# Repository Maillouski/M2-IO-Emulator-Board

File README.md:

# M2 IO Emulator Board

**English** | [Français](README.fr.md)

A drop-in replacement for the **Sega 837-10539 I/O board** of the **Daytona USA twin** cabinet (Sega Model 2), built around an
**Arduino Mega 2560**. It lets an emulator drive the original cabinet: controls, lamps, meters, the original drive board (force
feedback) and the original arcade monitor.

> **Status: prototype.** The design passes DRC and ERC, but no board has been built or tested yet. Read
> [Open points](#open-points) before you order.

**Version: V3.2** (2026-10-16). V3 adds an [HDMI input](#hdmi-input-v3) with its own HDMI → VGA converter, a stereo audio
output and a [composite sync](#composite-sync) that no longer depends on the polarity of H and V. V2 (screen jumper JP8) is kept under the tag [`v2`](https://github.com/Maillouski/M2-IO-Emulator-Board/tree/v2), and V1,
the first board, ordered from JLCPCB on 2026-10-13, under the tag [`v1`](https://github.com/Maillouski/M2-IO-Emulator-Board/tree/v1).

## What it does

The idea is simple: pull the Sega I/O board out of the cabinet and put this one in its place. It has the same size, the same
mounting holes and the same connector names, so the original harness plugs straight in. Nothing gets cut or rewired.

Once it's in, the Arduino Mega becomes the bridge between the emulator and the cabinet. It reads the controls and drives
everything the original board used to drive:

- **Controls** — steering, accelerator, brake, shifter, coin, START, the VR view buttons, TEST and SERVICE.
- **Lamps, meters and relay** — switched by a ULN2803A, so the original bulbs and coin meters keep working.
- **Force feedback** — the original drive board stays in the cabinet and gets its commands from the Mega, so the wheel keeps
  its original force feedback.
- **Video** — an HDMI input (V3) or a VGA input goes to the original arcade monitor, with composite sync built on the board
  (negative, whatever the H/V polarity). A small switchable video amplifier lifts the signal to the level the tube expects.
- **Sound** — the audio carried by the HDMI input comes out on two RCA jacks (V3).

A few practical details make bring-up easier: TEST and SERVICE buttons right on the board, a power LED, test points for each
supply, and a jumper (JP1) to choose whether the drive board logic runs from the Mega's 5 V or from the cabinet's.

## Video jumpers

| VIDEO IN (J13) | JP2-JP4 (VIDEO AMP) | JP5-JP7 (VGA TERM 75 Ω) |
|---|---|---|
| PC / HDMI-VGA adapter | ON | ON |
| Arcade RGB | OFF | OFF |

The same table is printed on the board. With the HDMI input (V3), use the first row: U4 is the same kind of chip as the one inside an HDMI-to-VGA
adapter (not yet tried on a real board).

## Composite sync

U2 (74HCT86) builds the composite sync for the monitor from H and V, after the circuit of
[Tomi Engdahl](https://www.epanorama.net/circuits/vga2rgbs.html), pointed out by Zebidee on the ArcadeControls.com forum. Each sync is compared (XOR) with its own average, taken by an
RC filter (R66 + C47 for H, R67 + C48 for V: 2.2 kΩ, 22 µF), so its pulses always come out positive; the two are then combined
and inverted. The result is a **negative** composite sync whatever the polarity of H and V at the input, which is what the
original monitor expects. After a change of polarity (new video mode), the filters settle within a fraction of a second. It
goes to VIDEO OUT through R47 (470 Ω).

## HDMI input (V3)

New in V3. J15 takes the host's HDMI output directly; U4 (CS5213) turns it into analog R/G/B with H/V sync and stereo audio, so
no external HDMI → VGA adapter is needed. The VGA input J13 is still there, and a jumper chooses between the two.

| Jumper | Setting | Effect |
|---|---|---|
| JP9 (VIDEO INPUT SOURCE) | ON | video from the HDMI input (J15, through U4) |
| JP9 | OFF | video from the VGA input (J13), as on V2 |
| JP10 (HDMI CHIP 5V SELECT) | 1-2 | U4 runs from the Mega's 5 V |
| JP10 | 2-3 | U4 runs from the cabinet's 5 V, through a ferrite filter (FB1) |

- The switch is made by U7 (TS5V330, R/G/B) and U8 (74HCT157, H/V sync); everything after it (amplifier, composite sync, VIDEO
  OUT) is the same as on V2.
- **Audio:** J16, a stacked RCA jack: **top = left**, **bottom = right**, AC-coupled (10 µF in series). The footprint takes a
  Same Sky RCJ-2223 (DigiKey; red on top, so red = left) or a Lian Xin XDJK-0271-1650 (LCSC C7527522; white on top, red at the bottom).
- **Hot plug:** HPD is pulled up to the HDMI cable's 5 V, so the host sees a display as soon as the cable is in.
- **EDID:** U6, an AT24C02 EEPROM on the HDMI DDC lines (address 0x50, decoupled by C24), is fitted and comes **blank**; U4's own
  DDC pins are not connected. The host must write a 256-byte EDID into it (the monitor's video mode, and HDMI audio if wanted):
  while it is blank, the host reads an invalid EDID. Its write protect is tied low, so it is programmed in place, through the
  HDMI cable.
- **U5** is a second, not fitted, footprint for an NX3303X converter. Fit U4 or U5, never both.

## Screen jumper (JP8)

New in V2. JP8 ties the Mega's D36 pin to ground. The Mega reads it with its internal pull-up and sends it to the host with the
other inputs, so the host can choose its screen at start-up. Once the board is in the cabinet, switching screens only takes the
jumper, not a software change.

| JP8 | Screen |
|---|---|
| ON | CRT (4:3): the original arcade monitor, through the HDMI input (V3) or an HDMI-to-VGA adapter |
| OFF | LVDS panel (16:9) |

Printed on the board as SCREEN / ON = CRT (4:3) / OFF = LVDS 16:9. What the host does with this input is up to the host
software (see [Driving it from a computer](#driving-it-from-a-computer)).

## Driving it from a computer

The board comes with its Arduino Mega program ([`firmware/`](firmware/m2io-mega)) and a test console
([`tools/m2io_console.py`](tools/m2io_console.py)). To run Daytona USA on your own computer or emulator build and reach the
cabinet through this board, read **[Driving the board from your own host](docs/HOST-PROTOCOL.md)**: serial link, frames,
byte meanings, how to connect them to MAME's emulated I/O board, and the pitfalls to avoid.

## 3D views

Rendered with KiCad 10 from the files in this repository.

| | |
|---|---|
|  |  |
| Perspective view | Video section: VGA and HDMI inputs, source switch, OPA3355 amplifier, jumpers and settings tables |
|  |  |
| Top | Bottom |

## Repository

| Path | Contents |
|---|---|
| `kicad/` | KiCad 10 project: schematic, PCB, design rules, project footprint library (`interface-borne.pretty`), 3D models |
| `fabrication/` | Gerbers, Excellon drill files and drill maps (`gerbers/`), the same files zipped for the fab, pick-and-place file; JLCPCB BOM and CPL for SMD assembly ([`jlcpcb/`](fabrication/jlcpcb/README.md)) |
| `firmware/` | Arduino Mega program (`m2io-mega/`) and its PC test without a Mega (`test/`) |
| `tools/` | Test console: plays the host's part from any computer (Python 3 + pyserial) |
| `bom/` | Full BOM ([`BOM.md`](bom/BOM.md)) and DigiKey import file ([`BOM-digikey.csv`](bom/BOM-digikey.csv)) |
| `docs/` | [Host protocol](docs/HOST-PROTOCOL.md), schematic PDF, board renders |

Board: 2 layers, 180 × 190 mm. Gerbers come from the PCB's own plot settings (KiCad 10).

## Open points

- **V3 has not been built.** U4 (CS5213) has not been tried with the 24 kHz mode of the arcade monitor (its datasheet gives a
  25-200 MHz TMDS clock range); the HDMI pairs run on a 2-layer board without controlled impedance. V1 is the only board that
  has been ordered.
- **U4 is soldered by hand** and comes from a grey-market source (see the [BOM](bom/BOM.md#u4-cs5213)). Its exposed pad has vias:
  order "Epoxy Filled & Capped" vias or reduce the paste.
- **U5 (NX3303X):** its pinout comes from the maker's published pin diagram; it has not been checked on a real chip.
- **CN1 and CN2** are plain 3M four-wall headers, without ejector latches.

## 3D models

The Arduino Mega model in `kicad/3d/` is derived from Arduino's CAD files (CC BY-SA 4.0) and KiCad library models; see
[`kicad/3d/README.md`](kicad/3d/README.md). The JST NH connectors and the RCA jack (J16, drawn as the RCJ-2223) use simplified models made for this project.

## Credits

Sources used for this board: SEGA Daytona USA manuals; MAME (Dirk Best for the Model 1 I/O board; R. Belmont, O. Galibert,
ElSemi, A. Salese, M. Daniels for Model 2); M2Pac by BigPanik (Gamoover); DaytonaUSB by SailorSat; BackForceFeeder by njz3; MEGA
adapters by Tibal; the MiSTer project (video to arcade monitor); Tomi Engdahl (composite sync circuit); Zebidee on the ArcadeControls.com forum.

Not affiliated with or endorsed by SEGA.

## License

© 2026 Nicolas Mailloux. **CC BY-NC-SA 4.0** — see [`LICENSE`](LICENSE).
You may build, use, modify and share this board, as long as you credit the author, keep the credits, and share changes under the
same license. **No commercial use**: don't sell the board, the files or a derivative.
The firmware and the tools are under the same license.

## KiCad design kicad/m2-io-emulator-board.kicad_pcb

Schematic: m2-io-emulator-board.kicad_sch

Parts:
C1, C2, C3, C4, C5, C6, C7, C8, C9, C10, C11, C12, C13, C14, C15, C16, C18, C20, C21, C22, C24, C27, C28, C29, C31, C33, C35, C36, C38, C43, C44, C46: 100 nF; C_0805_2012Metric; MPN CC0805KRX7R9BB104
C17: 100 µF 16 V; CP_Radial_D6.3mm_P2.50mm; MPN EEU-FC1C101H
C19, C23, C25, C26, C30, C32, C34, C37, C41, C42, C45: 10 µF; C_0805_2012Metric; MPN CL21A106KAYNNNE
C39, C40: 10 nF; C_0805_2012Metric; MPN CC0805KRX7R9BB103
C47, C48: 22 µF; C_0805_2012Metric; MPN CL21A226MOCLRNC
D1: LED verte 3 mm; LED_D3.0mm; MPN_CMS_Flux LTST-C170KGKT
FB1: 600 Ω @ 100 MHz; L_0805_2012Metric; MPN GZ2012D601TF
J1: N2550-6002-RB; IDC-Header_2x25_P2.54mm_Vertical; MPN N2550-6002-RB
J2: N2526-6002-RB; IDC-Header_2x13_P2.54mm_Vertical; MPN N2526-6002-RB
J3: B10P-SHF-1AA; JST_NH_B10P-SHF-1AA_1x10_P2.50mm_Vertical; MPN B10P-SHF-1AA
J4, J5: B12P-SHF-1AA; JST_NH_B12P-SHF-1AA_1x12_P2.50mm_Vertical; MPN B12P-SHF-1AA
J6, J7, J8, J9, J10: 61300811121; PinHeader_1x08_P2.54mm_Vertical; MPN 61300811121
J11: 61301011121; PinHeader_1x10_P2.54mm_Vertical; MPN 61301011121
J12: Pin Header 02x18 2.54mm Vertical; PinHeader_2x18_P2.54mm_Vertical; MPN Pin Header 02x18 2.54mm Vertical
J13: VGA femelle; DSUB-15-HD_Socket_Horizontal_P2.29x2.54mm_EdgePinOffset8.35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; MPN L77HDE15SD1CH4F
J14: VIDEO; JST_NH_B5P-SHF-1AA_1x05_P2.50mm_Vertical; MPN B5P-SHF-1AA
J15: HDMI A; HDMI_A_Amphenol_10029449-x01xLF_Horizontal; MPN 10029449-111RLF
J16: XDJK-0271-1650; RCA_Dual_Stacked_RCJ-22xx_XDJK-0271-1650; MPN XDJK-0271-1650
JP1, JP2, JP3, JP4, JP10: 61300311121; PinHeader_1x03_P2.54mm_Vertical; MPN 61300311121
JP5, JP6, JP7, JP8, JP9: 61300211121; PinHeader_1x02_P2.54mm_Vertical; MPN 61300211121
R1, R2, R3, R4, R5, R6, R7, R8, R9, R10, R11, R12, R13: 4,7 kΩ; R_0805_2012Metric; MPN RC0805FR-074K7L
R14, R15, R16, R17, R18, R19, R20, R21, R22, R23, R24, R25, R26, R27, R28, R29, R30, R31, R32, R33, R34, R35, R36, R37, R46, R60: 1 kΩ; R_0805_2012Metric; MPN RC0805FR-071KL
R38, R39, R40, R41, R42, R43, R44, R45, R61, R62, R63, R64, R65: 10 kΩ; R_0805_2012Metric; MPN RC0805FR-0710KL
R47: 470 Ω; R_0805_2012Metric; MPN RMCF0805FT470R
R48, R49, R50: 75 Ω; R_0805_2012Metric; MPN RC0805FR-0775RL
R51, R52, R53: 604 Ω; R_0805_2012Metric; MPN RC0805FR-07604RL
R54, R55, R56: 200 Ω; R_0805_2012Metric; MPN RC0805FR-07200RL
R57, R58, R59: 33 Ω; R_0805_2012Metric; MPN RC0805FR-0733RL
R66, R67: 2,2 kΩ; R_0805_2012Metric; MPN RC0805FR-072K2L
SH1, SH2, SH3, SH4, SH5, SH6, SH7, SH8, SH9, SH10: 382811-8; MPN 382811-8
SW1: TEST; SW_PUSH_6mm; MPN 1825910-6
SW2: SERVICE; SW_PUSH_6mm; MPN 1825910-6
TP1, TP2, TP3, TP4: 5002; TestPoint_Keystone_5000-5004_Miniature; MPN 5002
U1: ULN2803A; DIP-18_W7.62mm; MPN ULN2803A
U2: 74HCT86; SOIC-14_3.9x8.7mm_P1.27mm; MPN 74HCT86D,653
U3: OPA3355EA; TSSOP-14_4.4x5mm_P0.65mm; MPN OPA3355EA/2K5
U4: CS5213; QFN-32-1EP_4x4mm_P0.4mm_EP2.65x2.65mm; MPN CS5213AN
U5: NX3303X; QFN-32-1EP_5x5mm_P0.5mm_EP3.1x3.1mm; MPN NX3303X; not fitted
U6: AT24C02; SOIC-8_3.9x4.9mm_P1.27mm; MPN AT24C02C-SSHM-T
U7: TS5V330; TSSOP-16_4.4x5mm_P0.65mm; MPN TS5V330CPWR
U8: 74HCT157; SOIC-16_3.9x9.9mm_P1.27mm; MPN SN74HCT157DR

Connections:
/+5V_BORNE: C17.1, C18.1, FB1.1, J1.34, J1.36, J1.38, J1.50, J3.1, J3.2, J3.3, J3.4, JP1.3, R46.1, TP2.1 (1_1), U1.10 (COMMON_FREE__WHEELING_DIODES)
/+5V_BORNE_F: C45.1, C46.1, FB1.2, JP10.3
/+5V_CONV: C25.1, C32.1, C33.1, JP10.2, U4.10 (VDD5_IN), U5.22 (VDD5)
/+5V_MEGA: C19.1, C20.1, C21.1, C22.1, C23.1, C43.1, C44.1, J2.1, J2.7, J6.5, J12.1 (Pin_2), J12.2 (Pin_1), JP1.1, JP10.1, R1.1, R2.1, R3.1, R4.1, R5.1, R6.1, R7.1, R8.1, R9.1, R10.1, R11.1, R12.1, R13.1, R38.1, R39.1, R40.1, R41.1, R42.1, R43.1, R44.1, R45.1, R61.2, TP3.1 (1_1), U2.10 (3B), U2.14 (VCC), U3.1 (ENA), U3.2 (ENB), U3.3 (ENC), U3.4 (V+), U7.16 (VCC), U8.16 (VCC)
/AMP_B: JP4.1, R59.2
/AMP_FB_B: R53.2, R56.1, U3.13 (-INC)
/AMP_FB_G: R52.2, R55.1, U3.9 (-INB)
/AMP_FB_R: R51.2, R54.1, U3.6 (-INA)
/AMP_G: JP3.1, R58.2
/AMP_OUT_B: R53.1, R59.1, U3.14 (OUTC)
/AMP_OUT_G: R52.1, R58.1, U3.8 (OUTB)
/AMP_OUT_R: R51.1, R57.1, U3.7 (OUTA)
/AMP_R: JP2.1, R57.2
/AN_ACCEL: J2.4, R28.1
/AN_BRAKE: J2.9, R29.1
/AN_STEER: J2.3, R27.1
/AUD_OUT_L: C41.2, J16.3 (X1_HAUT)
/AUD_OUT_R: C42.2, J16.2 (X2_BAS)
/CSYNC_N: R47.1, U2.8 (3Y)
/CSYNC_XOR: U2.9 (3A), U2.11 (4Y)
/CS_3V3: C26.1, C27.1, C28.1, C29.1, U4.9 (VDD33_OUT), U4.15 (VDD33), U4.16 (AUDIO_EN), U4.20 (VDD33_VDAC), U4.21 (AVD_ADAC), U4.32 (VDD33)
/CS_AUD_VREF: C30.1, C31.1, U4.23 (AUD_VREF)
/DRV_I0: J4.2, R30.1
/DRV_I1: J4.3, R31.1
/DRV_I2: J4.4, R32.1
/DRV_I3: J4.5, R33.1
/DRV_I4: J4.7, R34.1
/DRV_I5: J4.8, R35.1
/DRV_I6: J4.9, R36.1
/DRV_I7: J4.10, R37.1
/DRV_O0: J5.2, J12.4 (Pin_3)
/DRV_O1: J5.3, J12.3 (Pin_4)
/DRV_O2: J5.4, J12.6 (Pin_5)
/DRV_O3: J5.5, J12.5 (Pin_6)
/DRV_O4: J5.7, J12.8 (Pin_7)
/DRV_O5: J5.8, J12.7 (Pin_8)
/DRV_O6: J5.9, J12.10 (Pin_9)
/DRV_O7: J5.10, J12.9 (Pin_10)
/GND: C1.2, C2.2, C3.2, C4.2, C5.2, C6.2, C7.2, C8.2, C9.2, C10.2, C11.2, C12.2, C13.2, C14.2, C15.2, C16.2, C17.2, C18.2, C19.2, C20.2, C21.2, C22.2, C23.2, C24.2, C25.2, C26.2, C27.2, C28.2, C29.2, C30.2, C31.2, C32.2, C33.2, C34.2, C35.2, C36.2, C37.2, C38.2, C39.2, C40.2, C43.2, C44.2, C45.2, C46.2, C47.2, C48.2, D1.1 (K), J1.2, J1.4, J1.6, J1.10, J1.26, J2.6, J2.11, J3.7, J3.8, J3.9, J3.10, J4.12, J6.6, J6.7, J11.4, J12.35 (Pin_36), J12.36 (Pin_35), J13.5 (GND), J13.6 (R_GND), J13.7 (V_GND), J13.8 (B_GND), J13.10 (SYNC_GND), J13.SH (BLINDAGE), J14.5 (GND), J15.2 (D2S), J15.5 (D1S), J15.8 (D0S), J15.11 (CKS), J15.17 (GND), J15.SH (SHIELD), J16.1 (BARREL), JP5.2, JP6.2, JP7.2, JP8.2, JP9.2, R54.2, R55.2, R56.2, R62.2, R63.2, R64.2, R65.2, SW1.2, SW2.2, TP1.1 (1_1), U1.9 (GND), U2.7 (GND), U3.11 (V-), U4.33 (EPAD), U5.23 (GND), U5.33 (EPAD), U6.1 (A0), U6.2 (A1), U6.3 (A2), U6.4 (GND), U6.7 (WP), U7.8 (GND), U7.12 (DD), U7.13 (S2D), U7.14 (S1D), U7.15 (~EN), U8.8 (GND), U8.10 (3B), U8.11 (3A), U8.13 (4B), U8.14 (4A), U8.15 (~G)
/HDMI_5V: C24.1, J15.18 (+5V), R60.2, U6.8 (VCC)
/HDMI_CK_N: J15.12 (CK-), U4.1 (HDMI_CKN), U5.1 (RX_CK-)
/HDMI_CK_P: J15.10 (CK+), U4.2 (HDMI_CKP), U5.2 (RX_CK+)
/HDMI_D0_N: J15.9 (D0-), U4.3 (HDMI_D0N), U5.4 (RX_D0-)
/HDMI_D0_P: J15.7 (D0+), U4.4 (HDMI_D0P), U5.5 (RX_D0+)
/HDMI_D1_N: J15.6 (D1-), U4.5 (HDMI_D1N), U5.7 (RX_D1-)
/HDMI_D1_P: J15.4 (D1+), U4.6 (HDMI_D1P), U5.8 (RX_D1+)
/HDMI_D2_N: J15.3 (D2-), U4.7 (HDMI_D2N), U5.9 (RX_D2-)
/HDMI_D2_P: J15.1 (D2+), U4.8 (HDMI_D2P), U5.10 (RX_D2+)
/HDMI_HPD: J15.19 (HPD), R60.1
/HDMI_SCL: J15.15 (SCL), U6.6 (SCL)
/HDMI_SDA: J15.16 (SDA), U6.5 (SDA)
/HD_AUD_L: C39.1, C41.1, U4.24 (AUD_L), U5.17 (AOUTL)
/HD_AUD_R: C40.1, C42.1, U4.22 (AUD_R), U5.18 (AOUTR)
/HD_B: U4.17 (VGA_B), U5.12 (B), U7.11 (S1C)
/HD_G: U4.18 (VGA_G), U5.13 (G), U7.5 (S1B)
/HD_HS: R62.1, U4.12 (VGA_HS), U5.27 (HSYNC), U8.2 (1A)
/HD_R: U4.19 (VGA_R), U5.14 (R), U7.2 (S1A)
/HD_VS: R63.1, U4.11 (VGA_VS), U5.24 (VSYNC), U8.5 (2A)
/HS_AVG: C47.1, R66.2, U2.2 (1B)
/HS_NORM: U2.3 (1Y), U2.13 (4B)
/IN_COIN1: C1.1, J1.1, R1.2, R14.1
/IN_COIN2: C2.1, J1.3, R2.2, R15.1
/IN_SERVICE: C4.1, J1.7, R4.2, R17.1, SW2.1
/IN_SH13: C10.1, J1.25, R10.2, R23.1
/IN_SH24: C11.1, J1.27, R11.2, R24.1
/IN_SH1234: C12.1, J1.29, R12.2, R25.1
/IN_SH_NU: C13.1, J1.31, R13.2, R26.1
/IN_START: C5.1, J1.9, R5.2, R18.1
/IN_TEST: C3.1, J1.5, R3.2, R16.1, SW1.1
/IN_VR1: C6.1, J1.11, R6.2, R19.1
/IN_VR2: C7.1, J1.13, R7.2, R20.1
/IN_VR3: C8.1, J1.15, R8.2, R21.1
/IN_VR4: C9.1, J1.17, R9.2, R22.1
/J13_B: J13.3 (B), U7.10 (S2C)
/J13_G: J13.2 (V), U7.6 (S2B)
/J13_HS: J13.13 (HSYNC), R64.1, U8.3 (1B)
/J13_R: J13.1 (R), U7.3 (S2A)
/J13_VS: J13.14 (VSYNC), R65.1, U8.6 (2B)
/LED_BORNE_A: D1.2 (A), R46.2
/MEGA_A0_STEER: C14.1, J7.1, R27.2
/MEGA_A1_ACCEL: C15.1, J7.2, R28.2
/MEGA_A2_BRAKE: C16.1, J7.3, R29.2
/MEGA_A8_METER1: J8.1, U1.1 (IN_1)
/MEGA_A9_METER2: J8.2, U1.2 (IN_2)
/MEGA_A10_LAMP_START: J8.3, U1.3 (IN_3)
/MEGA_A11_LAMP_VR1: J8.4, U1.4 (IN_4)
/MEGA_A12_LAMP_VR2: J8.5, U1.5 (IN_5)
/MEGA_A13_LAMP_VR3: J8.6, U1.6 (IN_6)
/MEGA_A14_LAMP_VR4: J8.7, U1.7 (IN_7)
/MEGA_A15_LEADER: J8.8, U1.8 (IN_8)
/MEGA_D10_DRV_I4: J11.8, R34.2, R42.2
/MEGA_D11_DRV_I5: J11.7, R35.2, R43.2
/MEGA_D12_DRV_I6: J11.6, R36.2, R44.2
/MEGA_D13_DRV_I7: J11.5, R37.2, R45.2
/MEGA_D30_SH_NU: J12.12 (Pin_11), R26.2
/MEGA_D31_SH1234: J12.11 (Pin_12), R25.2
/MEGA_D32_SH24: J12.14 (Pin_13), R24.2
/MEGA_D33_SH13: J12.13 (Pin_14), R23.2
/MEGA_D36_ECRAN: J12.18 (Pin_17), JP8.1
/MEGA_D37_VR4: J12.17 (Pin_18), R22.2
/MEGA_D42_VR3: J12.24 (Pin_23), R21.2
/MEGA_D43_VR2: J12.23 (Pin_24), R20.2
/MEGA_D44_VR1: J12.26 (Pin_25), R19.2
/MEGA_D45_START: J12.25 (Pin_26), R18.2
/MEGA_D46_SERVICE: J12.28 (Pin_27), R17.2
/MEGA_D47_TEST: J12.27 (Pin_28), R16.2
/MEGA_D48_COIN2: J12.30 (Pin_29), R15.2
/MEGA_D49_COIN1: J12.29 (Pin_30), R14.2
/MEGA_D50_DRV_I3: J12.32 (Pin_31), R33.2, R41.2
/MEGA_D51_DRV_I2: J12.31 (Pin_32), R32.2, R40.2
/MEGA_D52_DRV_I1: J12.34 (Pin_33), R31.2, R39.2
/MEGA_D53_DRV_I0: J12.33 (Pin_34), R30.2, R38.2
/NX_1V2: C37.1, C38.1, U5.3 (VDD12), U5.20 (LDO1V2), U5.31 (DVDD12)
/NX_3V3: C34.1, C35.1, C36.1, U5.6 (VDD33), U5.11 (VDD33), U5.15 (VDD33), U5.19 (VDD33), U5.21 (LDO3V3), U5.32 (VDD33)
/OUT_LAMP_START: J1.37, U1.16 (OUT_3)
/OUT_LAMP_VR1: J1.39, U1.15 (OUT_4)
/OUT_LAMP_VR2: J1.41, U1.14 (OUT_5)
/OUT_LAMP_VR3: J1.43, U1.13 (OUT_6)
/OUT_LAMP_VR4: J1.45, U1.12 (OUT_7)
/OUT_LEADER: J1.47, U1.11 (OUT_8)
/OUT_METER1: J1.33, U1.18 (OUT_1)
/OUT_METER2: J1.35, U1.17 (OUT_2)
/SRC_SEL: JP9.1, R61.1, U7.1 (IN), U8.1 (~A/B)
/TERM_B: JP7.1, R50.2
/TERM_G: JP6.1, R49.2
/TERM_R: JP5.1, R48.2
/VCC_DRIVE: J1.42, J1.44, JP1.2, TP4.1 (1_1)
/VGA_B: JP4.3, R50.1, U3.12 (+INC), U7.9 (DC)
/VGA_G: JP3.3, R49.1, U3.10 (+INB), U7.7 (DB)
/VGA_HS: R66.1, U2.1 (1A), U8.4 (1Y)
/VGA_R: JP2.3, R48.1, U3.5 (+INA), U7.4 (DA)
/VGA_VS: R67.1, U2.5 (2B), U8.7 (2Y)
/VIDEO_SYNC: J14.4 (SYNC), R47.2
/VID_B: J14.3 (B), JP4.2
/VID_G: J14.2 (V), JP3.2
/VID_R: J14.1 (R), JP2.2
/VS_AVG: C48.1, R67.2, U2.4 (2A)
/VS_NORM: U2.6 (2Y), U2.12 (4A)

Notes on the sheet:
Boutons de la carte (2026-10-09) : SW1 = TEST, SW2 = SERVICE (comme SW6 et SW7 de la carte E/S d'origine), vers la masse ; anti-rebond par le conditionneur de l'entrée (4,7 kΩ / 100 nF / 1 kΩ).
Ampli vidéo R/V/B (2026-10-12) : U3 OPA3355, gain 4,02 (RF 604 Ω / RG 200 Ω), RS 33 Ω en sortie ; +5V_MEGA. JP2-JP4 (R, V, B) : 1-2 = AMP, 2-3 = DIR (VGA direct vers J14). JP5-JP7 : terminaison 75 Ω (R48-R50) en service si posé. Adaptateur HDMI → VGA (0,7 V) : AMP + JP5-JP7 posés. Source déjà au ni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
Choix de l'écran de l'hôte (2026-10-13, carte V2) : JP8 relie D36 du Mega (bit 1 de IN1, rappel interne) à la masse. Cavalier posé = HDMI vers le tube (24 kHz, 4:3) ; retiré = LVDS (16:9). Lu par l'hôte au démarrage, par le Mega.
V3 (2026-10-15, non publiée) : HDMI → VGA intégré. J15 HDMI → U4 CS5213 OU U5 NX3303X (jamais les deux) → U7/U8. JP9 SOURCE : posé = HDMI, retiré = VGA J13 (comme la V2). Sorties = VGA_R/G/B/HS/VS (U2, U3, JP2-JP4 inchangés). JP10 alim de la puce : 1-2 = +5V_MEGA, 2-3 = +5V_BORNE filtré (FB1). U6 E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
Bloc vidéo tube (2026-10-07) : VGA de l'adaptateur HDMI → VGA → synchro composite (74HCT86) → fiche vidéo du faisceau (J14). J14 « VIDEO » : ordre de la NH5P de la carte filtre 839-0683 (1 R, 2 V, 3 B, 4 SYNC, 5 GND). R48-R50 (75 Ω) posées depuis le 2026-10-12, en service par JP5-JP7 ; J14 R/V/B pa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
V3 (2026-10-16) : synchro indépendante de la polarité (T. Engdahl). U2 portes 1-2 : chaque synchro XOR sa moyenne (2,2 kΩ / 22 µF) → HS_NORM, VS_NORM en impulsions positives → porte 4 → porte 3 (inversion) : CSYNC négative quelles que soient les polarités H/V.

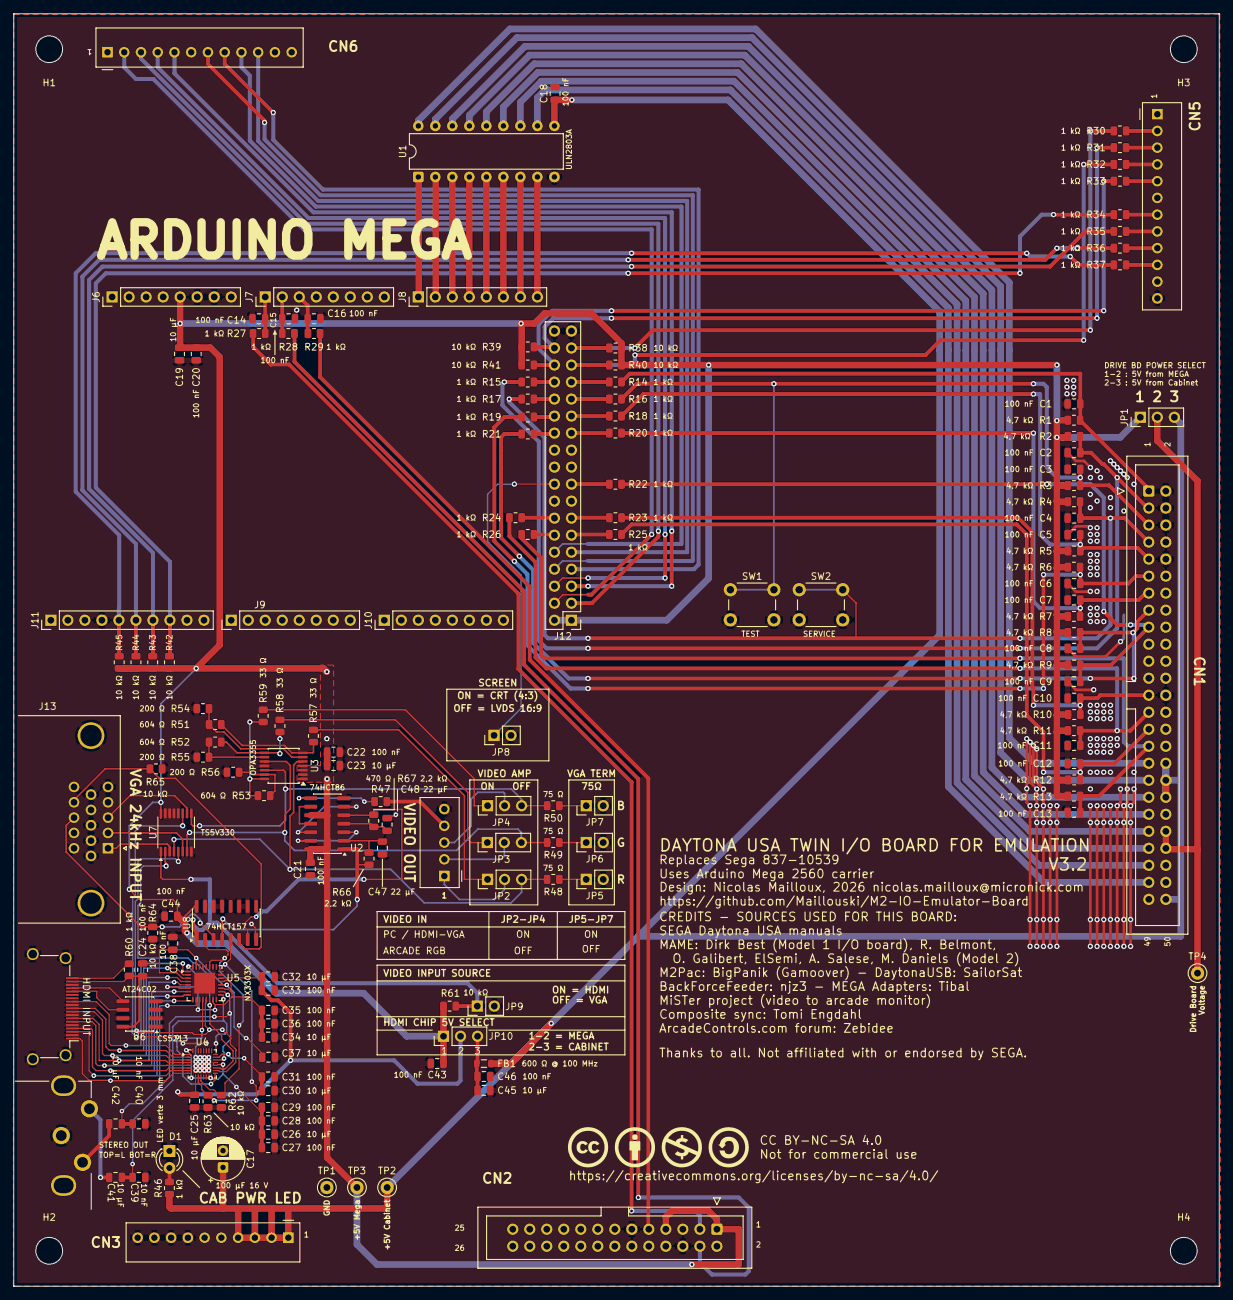
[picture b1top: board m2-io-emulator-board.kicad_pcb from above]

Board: 2 copper layers, 180.0 x 190.0 mm, 163 parts (0 on the bottom side), 138 nets.

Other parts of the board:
H1, H2, H3, H4: MountingHole_4.0mm
LOGO1: CC_BY-NC-SA_4.0
MEGA1: Arduino Mega 2560 (à l'envers); Arduino_Mega2560_3D

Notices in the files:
parts and their libraries:
Pictogrammes Creative Commons CC BY NC SA (icônes officielles, mirrors.creativecommons.org/presskit/icons) et mention de la licence CC BY-NC-SA 4.0, sérigraphie
https://creativecommons.org/licenses/by-nc-sa/4.0
